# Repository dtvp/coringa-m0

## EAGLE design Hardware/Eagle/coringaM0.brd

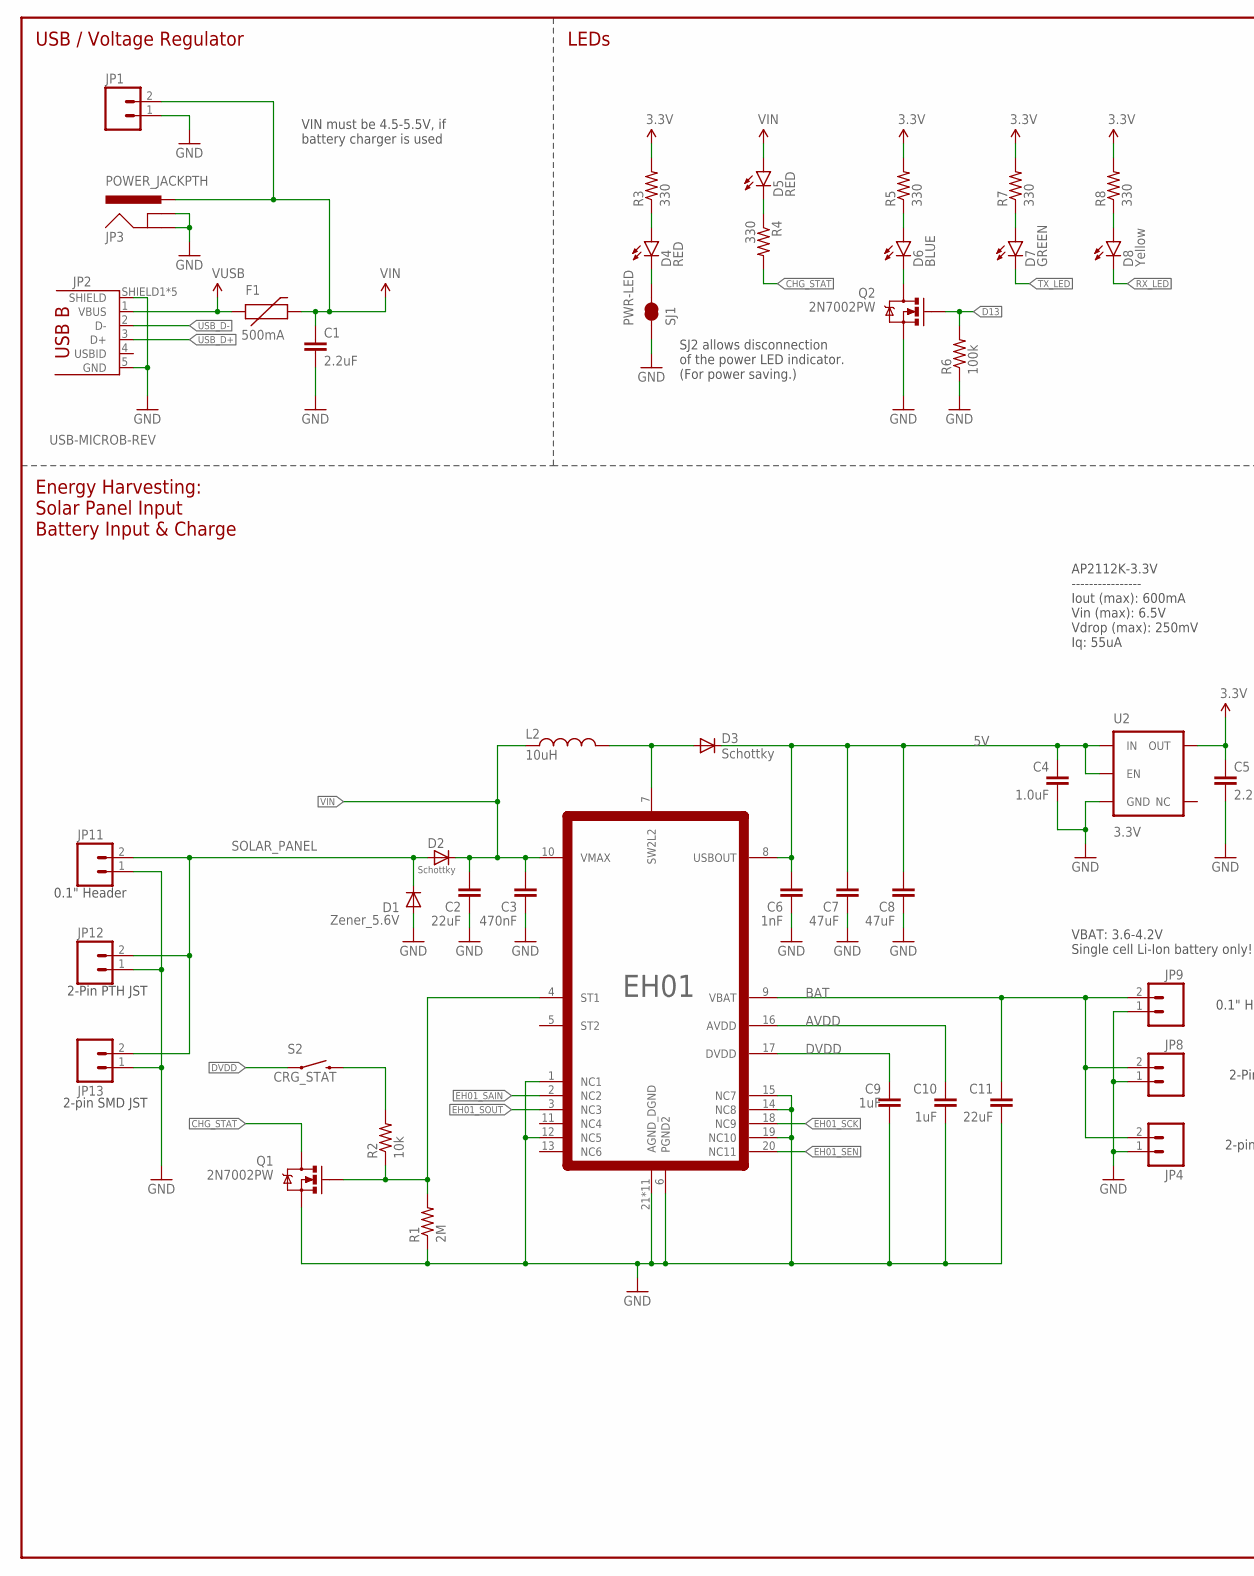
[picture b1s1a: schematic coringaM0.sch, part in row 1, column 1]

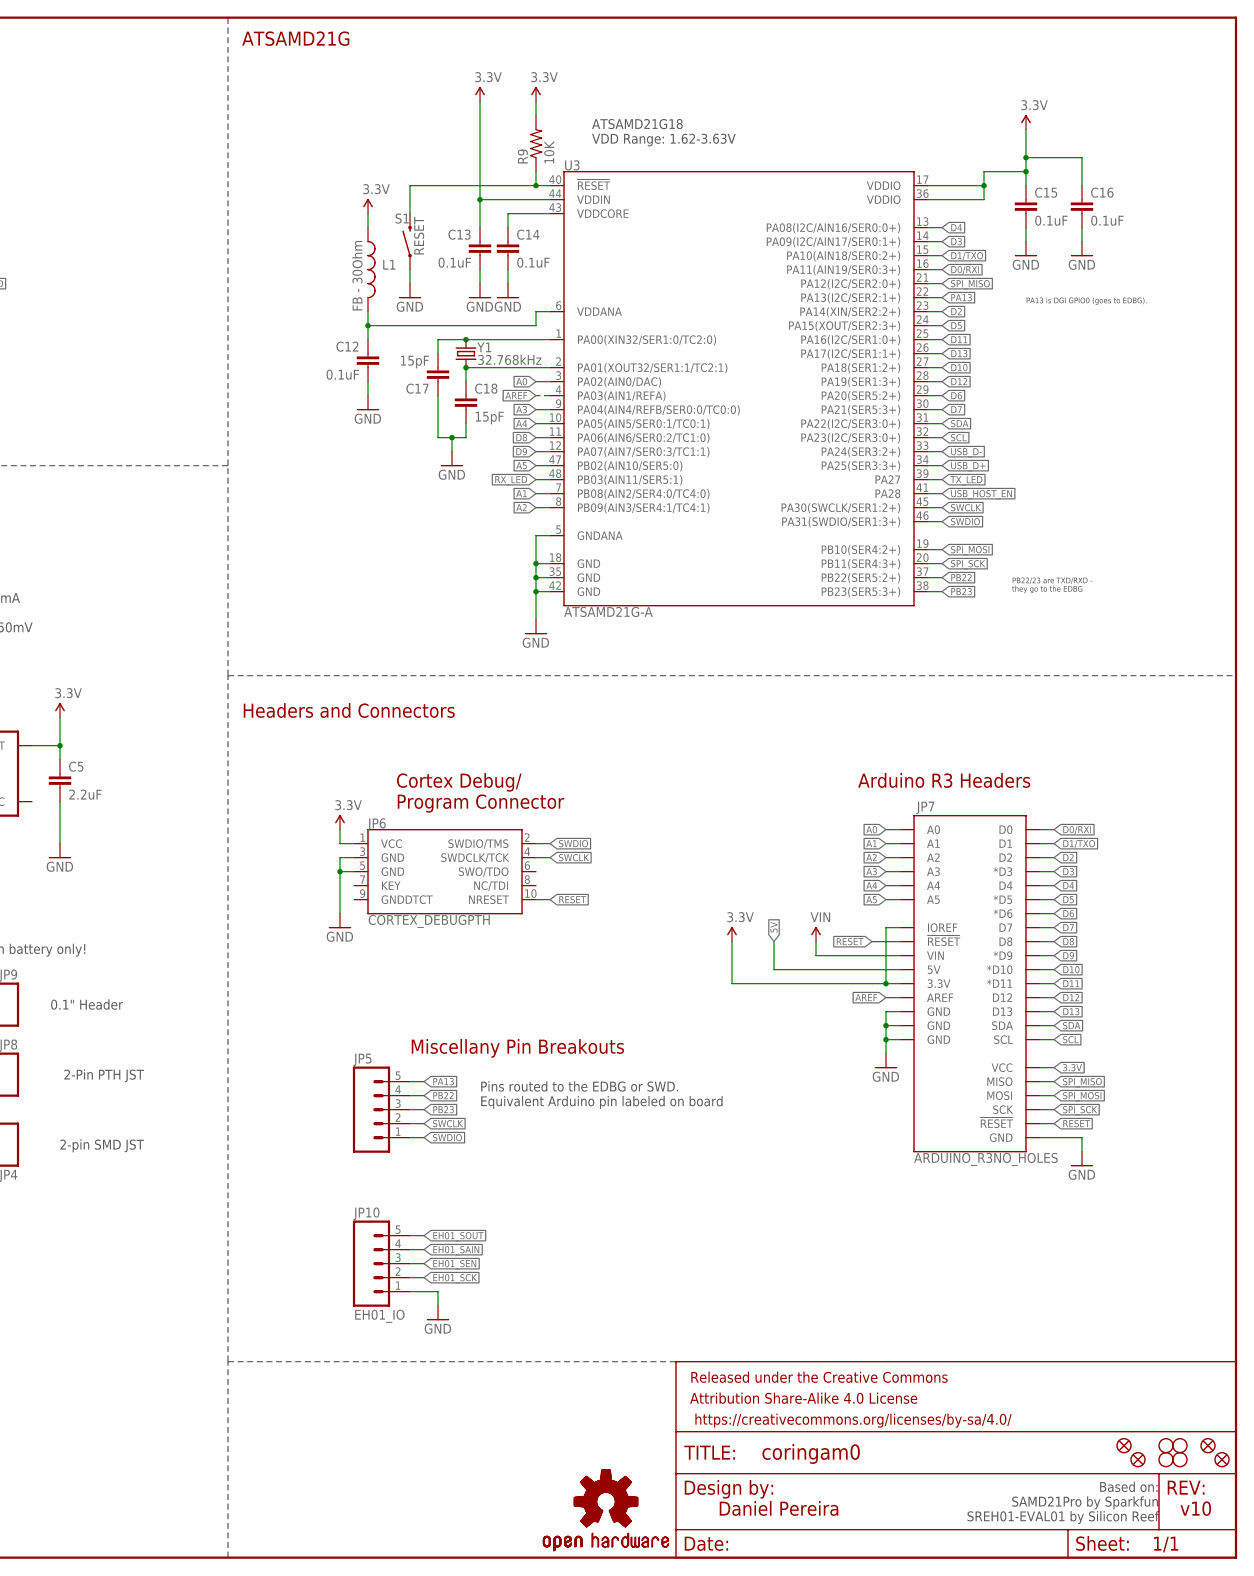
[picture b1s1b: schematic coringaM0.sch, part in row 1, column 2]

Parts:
C1, C5: 2.2uF; 1206
C2, C11: 22uF; RCL_C0805
C3: 470nF; RCL_C1206
C4: 1.0uF; 0805-CAP
C6: 1nF; RCL_C1206K
C7, C8: 47uF; RCL_C1206K
C9, C10: 1uF; RCL_C0402
C12, C13, C14, C15, C16: 0.1uF; 0603-CAP
C17, C18: 15pF; 0603-CAP
D1: Zener_5.6V; DO-214AC
D2, D3: Schottky; DO-214AC
D4, D5: RED; LED-0603
D6: BLUE; LED-0603
D7: GREEN; LED-0603
D8: Yellow; LED-0603
F1: 500mA; PTC-1206
FD1, FD2: FIDUCIAL-VIA
FID1, FID2: FIDUCIAL1X2; FIDUCIAL-1X2
FRAME1: FRAME-LEDGER; CREATIVE_COMMONS
JP1: M02PTH; 1X02
JP2: USB-MICROB-REV; USB-B-MICRO-REV-SMD
JP3: POWER_JACKPTH; POWER_JACK_PTH
JP4, JP13: M02-JST-2MM-SMT; JST-2-SMD
JP5: M05NO_SILK; 1X05_NO_SILK
JP6: CORTEX_DEBUGPTH; 2X5-PTH-1.27MM
JP7: ARDUINO_R3NO_HOLES; ARDUINO_R3_NO_HOLES
JP8, JP12: M02-JST-2-PTH-NO_SILK; JST-2-PTH-NS
JP9, JP11: M021X02_NO_SILK; 1X02_NO_SILK
JP10: EH01_IO; 1X05_NO_SILK
L1: FB - 30Ohm; 0603
L2: 10uH; SRN4065-100M
LOGO3: OSHW-LOGOS; OSHW-LOGO-S
LOGO4: OSHW-LOGOL; OSHW-LOGO-L
Q1, Q2: 2N7002PW; SOT323
R1: 2M; RESISTOR_R0402
R2: 10k; RESISTOR_R0402
R3, R4, R5, R7, R8: 330; 0603-RES
R6: 100k; 0603-RES
R9: 10K; 0603-RES
S1: RESET; TACTILE-SWITCH-SMD
S2: CRG_STAT; TACTILE-SWITCH-SMD
SJ1: PWR-LED; PAD-JUMPER-2-NC_BY_TRACE_NO_SILK
STANDOFF1, STANDOFF2, STANDOFF3, STANDOFF4: STAND-OFF
U1: EH01; QFN20
U2: 3.3V; SOT23-5
U3: ATSAMD21G-A; TQFP-48
Y1: 32.768kHz; CRYSTAL-SMD-3.2X1.5MM

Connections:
3.3V: C5.1, C13.1, C15.1, C16.1, JP6.1 (VCC), JP7.3.3V, JP7.IOREF, JP7.VCC, L1.1, R3.2, R5.2, R7.2, R8.2, R9.2, U2.5 (OUT), U3.17 (VDDIO), U3.36 (VDDIO), U3.44 (VDDIN)
5V: C4.1, C6.2, C7.2, C8.2, D3.C, JP7.5V, U1.8 (USBOUT), U2.1 (IN), U2.3 (EN)
!RESET: JP6.10 (NRESET), JP7.RESET@1 (!RESET!), JP7.RESET@2 (!RESET!), R9.1, S1.3 (2), U3.40 (!RESET!)
A0: JP7.A0, U3.3 (PA02(AIN0/DAC))
A1: JP7.A1, U3.7 (PB08(AIN2/SER4:0/TC4:0))
A2: JP7.A2, U3.8 (PB09(AIN3/SER4:1/TC4:1))
A3: JP7.A3, U3.9 (PA04(AIN4/REFB/SER0:0/TC0:0))
A4: JP7.A4, U3.10 (PA05(AIN5/SER0:1/TC0:1))
A5: JP7.A5, U3.47 (PB02(AIN10/SER5:0))
AREF: JP7.AREF, U3.4 (PA03(AIN1/REFA))
AVDD: C10.2, U1.16 (AVDD)
BAT: C11.2, JP4.2 (1), JP8.2, JP9.2, U1.9 (VBAT)
CHG_STAT: Q1.3 (D), R4.2
D0/RXI: JP7.D0, U3.16 (PA11(AIN19/SER0:3+))
D1/TXO: JP7.D1, U3.15 (PA10(AIN18/SER0:2+))
D2: JP7.D2, U3.23 (PA14(XIN/SER2:2+))
D3: JP7.D3 (*D3), U3.14 (PA09(I2C/AIN17/SER0:1+))
D4: JP7.D4, U3.13 (PA08(I2C/AIN16/SER0:0+))
D5: JP7.D5 (*D5), U3.24 (PA15(XOUT/SER2:3+))
D6: JP7.D6 (*D6), U3.29 (PA20(SER5:2+))
D7: JP7.D7, U3.30 (PA21(SER5:3+))
D8: JP7.D8, U3.11 (PA06(AIN6/SER0:2/TC1:0))
D9: JP7.D9 (*D9), U3.12 (PA07(AIN7/SER0:3/TC1:1))
D10: JP7.D10 (*D10), U3.27 (PA18(SER1:2+))
D11: JP7.D11 (*D11), U3.25 (PA16(I2C/SER1:0+))
D12: JP7.D12, U3.28 (PA19(SER1:3+))
D13: JP7.D13, Q2.1 (G), R6.2, U3.26 (PA17(I2C/SER1:1+))
DVDD: C9.2, S2.1, U1.17 (DVDD)
EH01_SAIN: JP10.4, U1.2 (NC2)
EH01_SCK: JP10.2, U1.18 (NC9)
EH01_SEN: JP10.3, U1.20 (NC11)
EH01_SOUT: JP10.5, U1.3 (NC3)
EH01_ST1: Q1.1 (G), R1.2, R2.1, U1.4 (ST1)
EH01_SW: D3.A, L2.P$2 (2), U1.7 (SW2L2)
GND: C1.2, C2.1, C3.1, C4.2, C5.2, C6.1, C7.1, C8.1, C9.1, C10.1, C11.1, C12.2, C13.2, C14.2, C15.2, C16.2, C17.1, C18.2, D1.A, JP1.1, JP2.5 (GND), JP2.SHIELD1 (SHIELD), JP2.SHIELD2 (SHIELD), JP2.SHIELD3 (SHIELD), JP2.SHIELD4 (SHIELD), JP2.SHIELD5 (SHIELD), JP3.GND, JP3.GNDBREAK, JP4.1 (2), JP6.3 (GND), JP6.5 (GND), JP7.GND@1 (GND), JP7.GND@2 (GND), JP7.GND@3 (GND), JP7.GND@4 (GND), JP8.1, JP9.1, JP10.1, JP11.1, JP12.1, JP13.1 (2), Q1.2 (S), Q2.2 (S), R1.1, R6.1, S1.1, SJ1.1, U1.1 (NC1), U1.6 (PGND2), U1.12 (NC5), U1.14 (NC8), U1.15 (NC7), U1.19 (NC10), U1.21 (AGND_DGND), U1.22 (AGND_DGND), U1.P$1 (AGND_DGND), U1.P$2 (AGND_DGND), U1.P$3 (AGND_DGND), U1.P$4 (AGND_DGND), U1.P$5 (AGND_DGND), U1.P$6 (AGND_DGND), U1.P$7 (AGND_DGND), U1.P$8 (AGND_DGND), U1.P$9 (AGND_DGND), U2.2 (GND), U3.5 (GNDANA), U3.18 (GND), U3.35 (GND), U3.42 (GND)
unnamed: C17.2, U3.1 (PA00(XIN32/SER1:0/TC2:0)), Y1.P$2 (2)
unnamed: D6.C, Q2.3 (D)
unnamed: C18.1, U3.2 (PA01(XOUT32/SER1:1/TC2:1)), Y1.P$1 (1)
unnamed: D4.A, R3.1
unnamed: D6.A, R5.1
unnamed: D5.C, R4.1
unnamed: D7.A, R7.1
unnamed: D8.A, R8.1
unnamed: D4.C, SJ1.2
unnamed: R2.2, S2.3 (2)
PA13: JP5.5, U3.22 (PA13(I2C/SER2:1+))
PB22: JP5.4, U3.37 (PB22(SER5:2+))
PB23: JP5.3, U3.38 (PB23(SER5:3+))
RX_LED: D8.C, U3.48 (PB03(AIN11/SER5:1))
SCL: JP7.SCL, U3.32 (PA23(I2C/SER3:0+))
SDA: JP7.SDA, U3.31 (PA22(I2C/SER3:0+))
SOLAR_PANEL: D1.C, D2.A, JP11.2, JP12.2, JP13.2 (1)
SPI_MISO: JP7.MISO, U3.21 (PA12(I2C/SER2:0+))
SPI_MOSI: JP7.MOSI, U3.19 (PB10(SER4:2+))
SPI_SCK: JP7.SCK, U3.20 (PB11(SER4:3+))
SWCLK: JP5.2, JP6.4 (SWDCLK/TCK), U3.45 (PA30(SWCLK/SER1:2+))
SWDIO: JP5.1, JP6.2 (SWDIO/TMS), U3.46 (PA31(SWDIO/SER1:3+))
TX_LED: D7.C, U3.39 (PA27)
USB_D+: JP2.3 (D+), U3.34 (PA25(SER3:3+))
USB_D-: JP2.2 (D-), U3.33 (PA24(SER3:2+))
USB_HOST_EN: U3.41 (PA28)
VDDANA: C12.1, L1.2, U3.6 (VDDANA)
VDDCORE: C14.1, U3.43 (VDDCORE)
VIN: C1.1, C2.2, C3.2, D2.C, D5.A, F1.2, JP1.2, JP3.PWR, JP7.VIN, L2.P$1 (1), U1.10 (VMAX)
VUSB: F1.1, JP2.1 (VBUS)

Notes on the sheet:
PB22/23 are TXD/RXD - they go to the EDBG
PA13 is DGI GPIO0 (goes to EDBG).
USB / Voltage Regulator
LEDs
Cortex Debug/ Program Connector
Arduino R3 Headers
ATSAMD21G
Daniel Pereira
v10
Energy Harvesting: Solar Panel Input Battery Input & Charge
SJ2 allows disconnection of the power LED indicator. (For power saving.)
Miscellany Pin Breakouts
Headers and Connectors
VIN must be 4.5-5.5V, if battery charger is used
ATSAMD21G18 VDD Range: 1.62-3.63V
Based on: SAMD21Pro by Sparkfun SREH01-EVAL01 by Silicon Reef
0.1" Header
2-Pin PTH JST
2-pin SMD JST
AP2112K-3.3V ---------------- Iout (max): 600mA Vin (max): 6.5V Vdrop (max): 250mV Iq: 55uA
Pins routed to the EDBG or SWD. Equivalent Arduino pin labeled on board
VBAT: 3.6-4.2V Single cell Li-Ion battery only\!

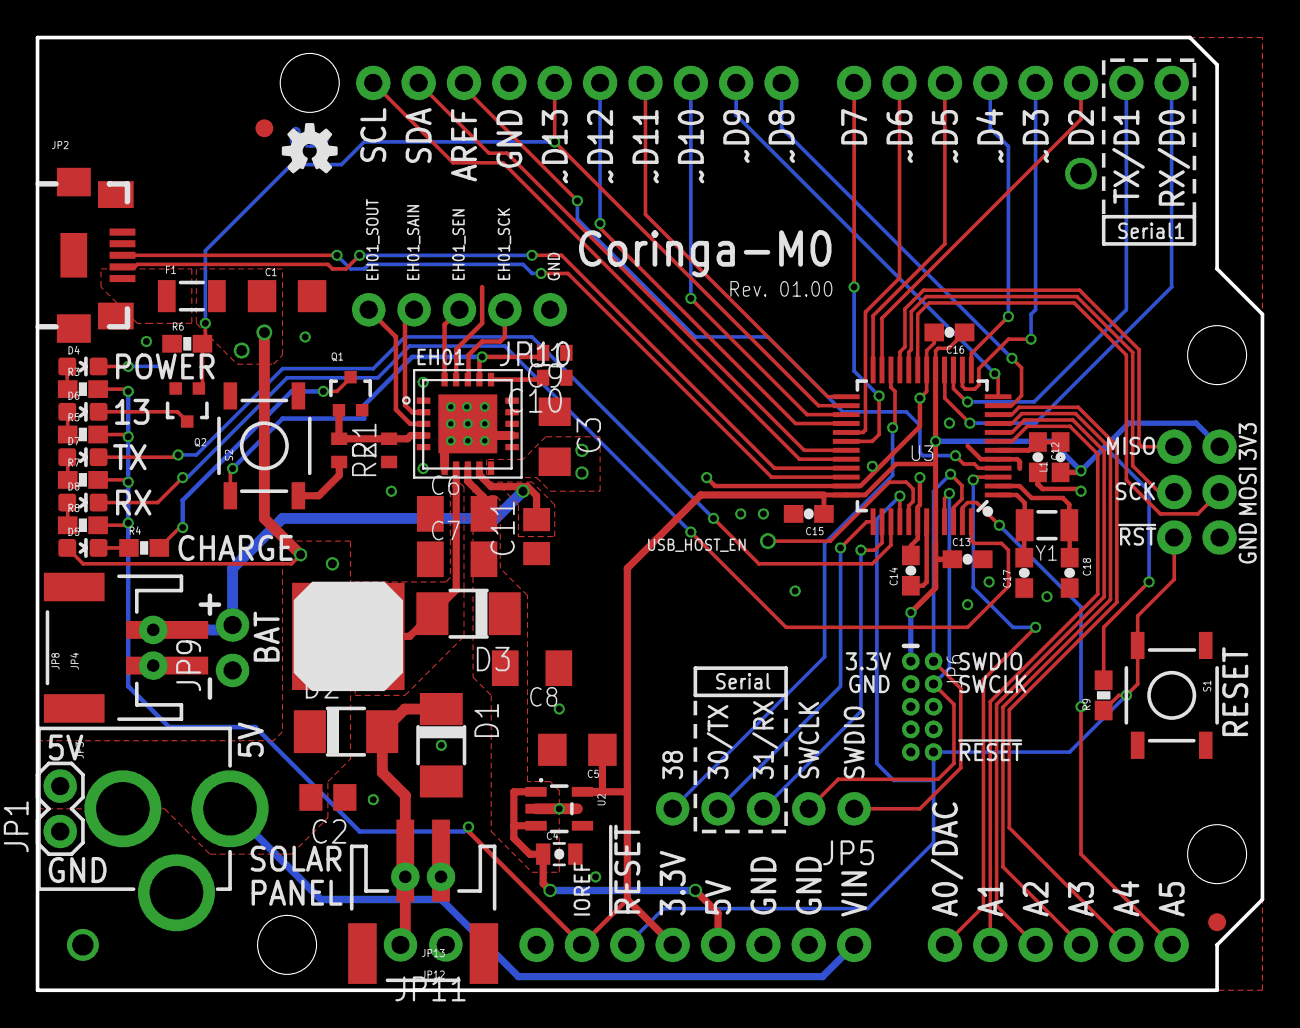
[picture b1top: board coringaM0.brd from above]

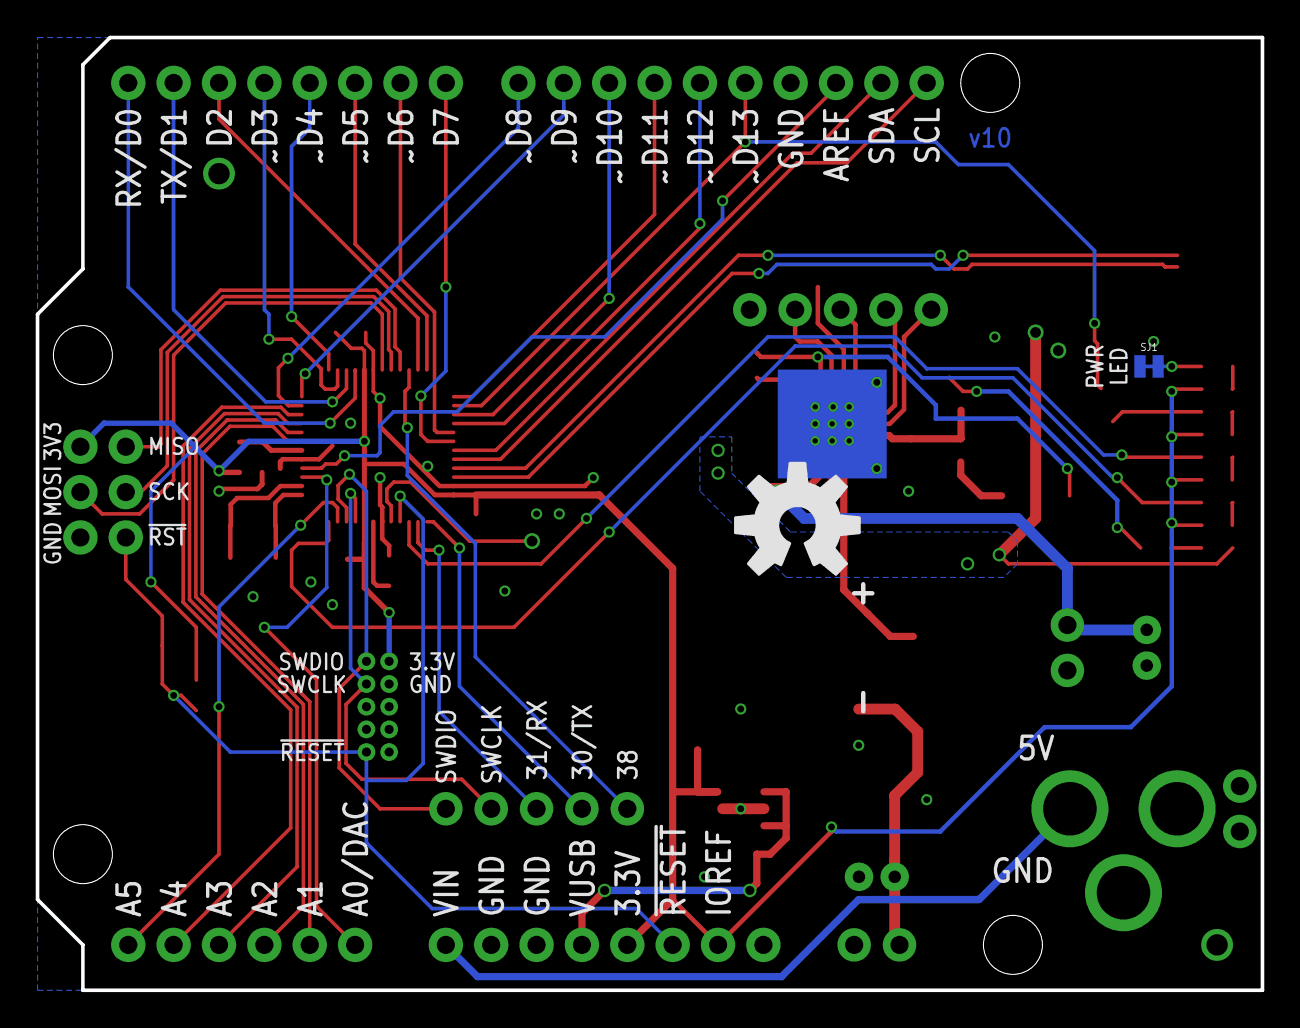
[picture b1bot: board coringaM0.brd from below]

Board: 2 copper layers, 68.6 x 53.3 mm, 71 parts (2 on the bottom side), 64 nets.

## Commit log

2016-01-29 Coringa-M0 Design Files.
2016-01-29 Added blink D13 sketch.
2016-01-30 Uploading presentation.

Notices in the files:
parts and their libraries:
SparkFun-Capacitors: Licensing: Creative Commons ShareAlike 4.0 International - https://creativecommons.org/licenses/by-sa/4.0
SparkFun-Aesthetics: Released under the Creative Commons Attribution Share-Alike 4.0 License
SparkFun-Aesthetics: https://creativecommons.org/licenses/by-sa/4.0
